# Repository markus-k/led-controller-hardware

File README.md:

#  12 channel LED controller (hardware files)

This repository contains all KiCad project files for my LED controller project. More information about this project can be found on [Hackaday.io](https://hackaday.io/project/47190-12-channel-led-controller).

## Known issues (rev 1.0)

* The 3.3V rail is missing a backup supply (from a big cap for example) and 12-24V presence detection to keep the µC and EEPROM alive for a few more milliseconds after the power went away. It's currently not possible to save the EEPROM on powerdown and thus periodic or event based writes are required, wearing the EEPROM more than needed.
* The 5A/Ch rating does not seem realistic unless smoking hot FETs are okay :)

## License

This project is licensed under the [TAPR Open Hardware License](LICENSE.txt). A copy of the license is included in this repository.

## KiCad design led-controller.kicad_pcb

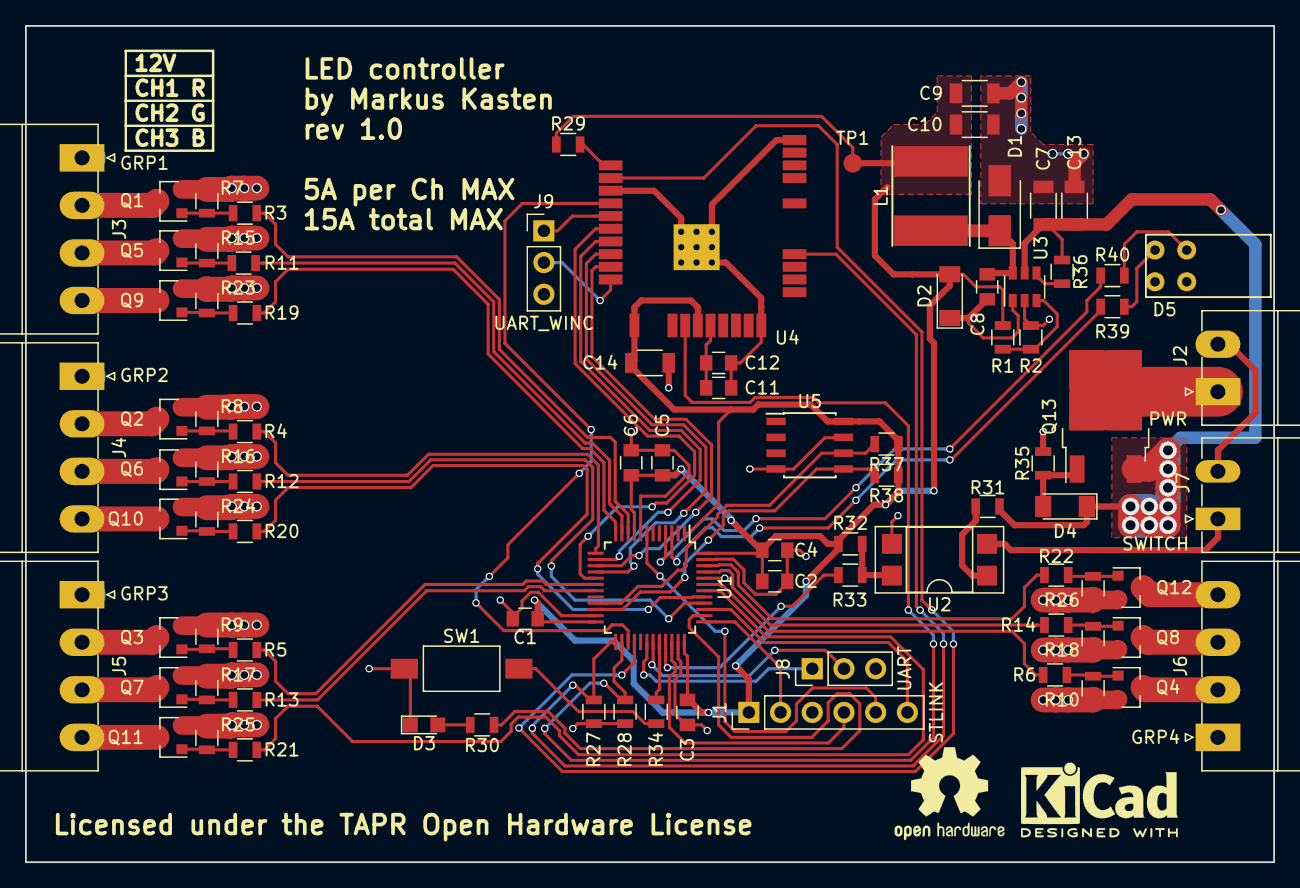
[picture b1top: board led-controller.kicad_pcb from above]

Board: 2 copper layers, 100.0 x 67.0 mm, 89 parts (0 on the bottom side), 77 nets.

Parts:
C1, C2, C3, C8: 100n; C_0805
C4: 4.7u; C_0805
C5, C12: 10n; C_0805
C6: 1u; C_0805
C7, C13: 4.7u; C_1206
C9, C10, C14: 10u; C_1206
C11: 10u; C_0805
D1: 1A 40V; D_SMA
D2: D; D_MiniMELF
D3: LED; LED_0805
D4: 10V; D_MiniMELF
D5: LED_Dual_AACC; MEN-1801
J1: STLINK; Pin_Header_Straight_1x06_Pitch2.54mm
J2: PWR; PhoenixContact_MC-G_02x3.81mm_Angled
J3: GRP1; PhoenixContact_MC-G_04x3.81mm_Angled
J4: GRP2; PhoenixContact_MC-G_04x3.81mm_Angled
J5: GRP3; PhoenixContact_MC-G_04x3.81mm_Angled
J6: GRP4; PhoenixContact_MC-G_04x3.81mm_Angled
J7: SWITCH; PhoenixContact_MC-G_02x3.81mm_Angled
J8: UART; Pin_Header_Straight_1x03_Pitch2.54mm
J9: UART_WINC; Pin_Header_Straight_1x03_Pitch2.54mm
L1: 15uH; Inductor_Taiyo-Yuden_NR-60xx_HandSoldering
Q1, Q2, Q3, Q4, Q5, Q6, Q7, Q8, Q9, Q10, Q11, Q12: Q_NMOS_GSD; SOT-23
Q13: DMP4015SK3; TO-252-2
R1: 31.2k; R_0805
R2, R32, R37, R38: 10k; R_0805
R3, R4, R5, R6, R11, R12, R13, R14, R19, R20, R21, R22: 100; R_0805
R7, R8, R9, R10, R15, R16, R17, R18, R23, R24, R25, R26, R35: 100k; R_0805
R27, R28, R29, R36: 1M; R_0805
R30, R31, R33, R34, R39, R40: 1k; R_0805
SW1: SW_Push; SW_SPST_FSMSM
TP1: TEST; Measurement_Point_Round-SMD-Pad_Small
U1: STM32F101C8Tx; LQFP-48_7x7mm_Pitch0.5mm
U2: LTV-814; DIP-4_W7.62mm_SMDSocket_SmallPads
U3: MCP16301; SOT-23-6
U4: ATWINC15x0
U5: 24LC16; SOIC-8_3.9x4.9mm_Pitch1.27mm

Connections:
+3V3: C1.1, C2.1, C3.1, C4.1, C5.1, C6.1, C9.1, C10.1, C14.1, D2.2, J1.1, L1.2, R1.1, R29.1, R32.1, R37.1, R38.1, TP1.1, U1.1, U1.9, U1.24, U1.36, U1.48, U4.20, U4.23, U5.8
+12V: C7.1, C13.1, D4.1, J3.1, J4.1, J5.1, J6.1, Q13.3, R31.1, R36.2, U3.5
/LED_driver/CH1: R3.2, U1.10
/LED_driver/CH2: R11.2, U1.11
/LED_driver/CH3: R19.2, U1.12
/LED_driver/CH4: R4.2, U1.13
/LED_driver/CH5: R12.2, U1.40
/LED_driver/CH6: R20.2, U1.41
/LED_driver/CH7: R5.2, U1.18
/LED_driver/CH8: R13.2, U1.19
/LED_driver/CH9: R21.2, U1.42
/LED_driver/CH10: R6.2, U1.43
/LED_driver/CH11: R14.2, U1.45
/LED_driver/CH12: R22.2, U1.46
/MCU/ETH_IRQ: U1.27, U4.13
/MCU/ETH_RESET: R27.2, U1.25, U4.4
/MCU/ETH_WAKE: U1.28, U4.11
/MCU/I2C_SCL: R37.2, U1.21, U5.6
/MCU/I2C_SDA: R38.2, U1.22, U5.5
/MCU/NRST: J1.5, U1.7
/MCU/SPI_CS: U1.14, U4.16
/MCU/SPI_MISO: U1.16, U4.17
/MCU/SPI_MOSI: U1.17, U4.15
/MCU/SPI_SCK: U1.15, U4.18
/MCU/SWCLK: J1.2, U1.37
/MCU/SWDIO: J1.4, U1.34
/MCU/SWO: J1.6, U1.39
/MCU/UART_RX: J8.2, U1.31
/MCU/UART_TX: J8.1, U1.30
/Power/12V_IN: J2.1, Q13.2
/ethernet/ENABLE: R28.2, U1.26, U4.22
/ethernet/UART_RX: J9.2, U4.19
/ethernet/UART_TX: J9.1, U4.14
GND: C1.2, C2.2, C3.2, C4.2, C5.2, C6.2, C7.2, C9.2, C10.2, C11.2, C12.2, C13.2, C14.2, D1.2, D3.1, D5.3, D5.4, J1.3, J2.2, J7.2, J8.3, J9.3, Q1.2, Q2.2, Q3.2, Q4.2, Q5.2, Q6.2, Q7.2, Q8.2, Q9.2, Q10.2, Q11.2, Q12.2, R2.2, R7.2, R8.2, R9.2, R10.2, R15.2, R16.2, R17.2, R18.2, R23.2, R24.2, R25.2, R26.2, R27.1, R28.1, R35.2, SW1.1, U1.8, U1.23, U1.35, U1.44, U1.47, U2.3, U3.2, U4.9, U4.12, U4.28, U4.29, U5.4, U5.7
unnamed: C8.1, D2.1, U3.1
unnamed: C8.2, D1.1, L1.1, U3.6
unnamed: C11.1, C12.1, U4.24
unnamed: D3.2, R30.2
unnamed: D4.2, Q13.1, R35.1
unnamed: D5.1, R40.2
unnamed: D5.2, R39.2
unnamed: J3.2, Q1.3
unnamed: J3.3, Q5.3
unnamed: J3.4, Q9.3
unnamed: J4.2, Q2.3
unnamed: J4.3, Q6.3
unnamed: J4.4, Q10.3
unnamed: J5.2, Q3.3
unnamed: J5.3, Q7.3
unnamed: J5.4, Q11.3
unnamed: J6.2, Q4.3
unnamed: J6.3, Q8.3
unnamed: J6.4, Q12.3
unnamed: J7.1, U2.2
unnamed: Q1.1, R3.1, R7.1
unnamed: Q2.1, R4.1, R8.1
unnamed: Q3.1, R5.1, R9.1
unnamed: Q4.1, R6.1, R10.1
unnamed: Q5.1, R11.1, R15.1
unnamed: Q6.1, R12.1, R16.1
unnamed: Q7.1, R13.1, R17.1
unnamed: Q8.1, R14.1, R18.1
unnamed: Q9.1, R19.1, R23.1
unnamed: Q10.1, R20.1, R24.1
unnamed: Q11.1, R21.1, R25.1
unnamed: Q12.1, R22.1, R26.1
unnamed: R1.2, R2.1, U3.3
unnamed: R29.2, U4.10
unnamed: R30.1, U1.38
unnamed: R31.2, U2.1
unnamed: R32.2, R33.2, U2.4
unnamed: R33.1, U1.33
unnamed: R34.1, U1.32
unnamed: R34.2, SW1.2
unnamed: R36.1, U3.4
unnamed: R39.1, U1.3
unnamed: R40.1, U1.4

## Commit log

2018-02-09 Initial commit with project files
2018-02-09 Add README
2018-02-11 Add UART headers for mcu and winc
2018-02-20 Add TAPR Open Hardware License file
2018-02-20 Add license to silkscreen layer
2018-02-20 Add rendered board image for README
2018-02-20 Add rendered image to README
2018-02-25 Fix wrong pin in ATWINC symbol and add a cap to it's VCC
2018-02-26 Some final silkscreen fixes
2018-03-11 Adjust a couple of component values for consistency with the actual boards
2018-03-15 Use correct resistor value for opto-coupler
2018-03-15 Add PDF of schematic and a photo of the finished PCB
2018-04-13 Use correct values for feedback voltage divider in power supply
2018-05-27 add known issues section to README
